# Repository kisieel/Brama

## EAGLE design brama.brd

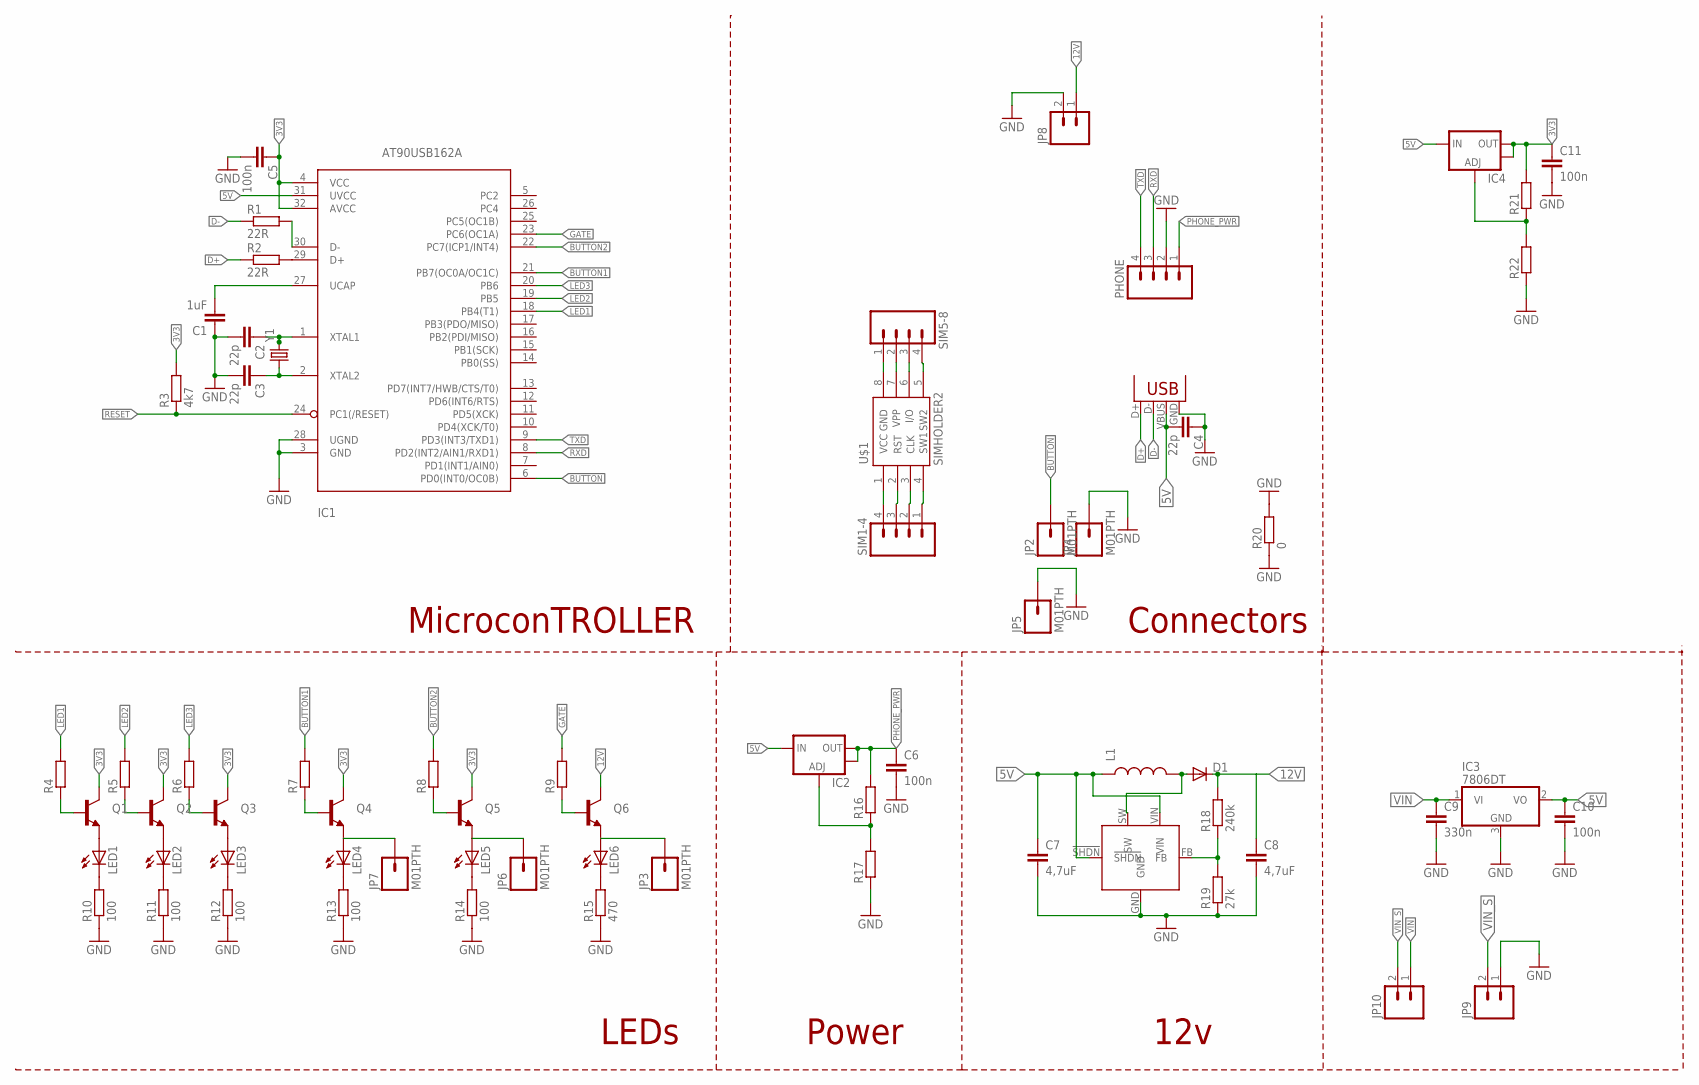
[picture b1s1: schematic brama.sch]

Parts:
C1: 1uF; C0805
C2, C3, C4: 22p; C0805
C5, C6, C10, C11: 100n; C0805
C7, C8: 4,7uF; C0805
C9: 330n; C0805
D1: DIODESMB; SMB-DIODE
IC1: AT90USB162A; TQFP32-08
IC2, IC4: V_REG_LM1117SOT223; SOT223
IC3: 7806DT; TO252
JP1: USBSMD; USB-MINIB
JP2, JP3, JP4, JP5, JP6, JP7: M01PTH; 1X01
JP8, JP9, JP10: M02PTH3; 1X02_LONGPADS
L1: INDUCTOR0805; 0805
LED1, LED2, LED3, LED4, LED5, LED6: LEDCHIPLED_0805; CHIPLED_0805
PHONE: M04LONGPADS; 1X04_LONGPADS
Q1, Q2, Q3, Q4, Q5, Q6: TRANSISTOR_NPNSOT23; SOT23
R1, R2: 22R; R0805
R3: 4k7; R0805
R4, R5, R6, R7, R8, R9, R16, R17, R21, R22: R-EU_R0805; R0805
R10, R11, R12, R13, R14: 100; R0805
R15: 470; R0805
R18: 240k; R0805
R19: 27k; R0805
R20: 0; R0805
SIM1-4, SIM5-8: M04LONGPADS; 1X04_LONGPADS
U$1: SIMHOLDER2
U$6: LM2704MF-ADJ; SOT23-5
Y1: CRYSTALSMD; HC49UP

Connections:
3V3: C5.1, C11.1, IC1.4 (VCC), IC1.32 (AVCC), IC4.2 (OUT), IC4.4 (OUT), Q1.3 (C), Q2.3 (C), Q3.3 (C), Q4.3 (C), Q5.3 (C), R3.2, R21.2
5V: C4.2, C7.1, C10.1, IC1.31 (UVCC), IC2.3 (IN), IC3.2 (VO), IC4.3 (IN), JP1.VBUS, L1.1, U$6.!SHDN, U$6.VIN
12V: C8.1, D1.C, JP8.1, Q6.3 (C), R18.2
BUTTON: IC1.6 (PD0(INT0/OC0B)), JP2.1
BUTTON1: IC1.21 (PB7(OC0A/OC1C)), R7.2
BUTTON2: IC1.22 (PC7(ICP1/INT4)), R8.2
D+: JP1.D+, R2.1
D-: JP1.D-, R1.1
GATE: IC1.23 (PC6(OC1A)), R9.2
GND: C1.1, C2.2, C3.2, C4.1, C5.2, C6.2, C7.2, C8.2, C9.2, C10.2, C11.2, IC1.3 (GND), IC1.28 (UGND), IC3.3 (GND), JP1.GND, JP4.1, JP5.1, JP8.2, JP9.1, PHONE.2, R10.1, R11.1, R12.1, R13.1, R14.1, R15.1, R17.1, R19.1, R20.1, R20.2, R22.1, U$6.GND
LED1: IC1.18 (PB4(T1)), R4.2
LED2: IC1.19 (PB5), R5.2
LED3: IC1.20 (PB6), R6.2
unnamed: IC1.30 (D-), R1.2
unnamed: IC1.29 (D+), R2.2
unnamed: C2.1, IC1.1 (XTAL1), Y1.2
unnamed: C3.1, IC1.2 (XTAL2), Y1.1
unnamed: SIM1-4.4, U$1.1 (VCC)
unnamed: LED1.A, Q1.2 (E)
unnamed: LED2.A, Q2.2 (E)
unnamed: LED3.A, Q3.2 (E)
unnamed: JP7.1, LED4.A, Q4.2 (E)
unnamed: JP6.1, LED5.A, Q5.2 (E)
unnamed: JP3.1, LED6.A, Q6.2 (E)
unnamed: Q1.1 (B), R4.1
unnamed: Q2.1 (B), R5.1
unnamed: Q3.1 (B), R6.1
unnamed: Q4.1 (B), R7.1
unnamed: Q5.1 (B), R8.1
unnamed: Q6.1 (B), R9.1
unnamed: LED1.C, R10.2
unnamed: LED2.C, R11.2
unnamed: LED3.C, R12.2
unnamed: LED4.C, R13.2
unnamed: LED5.C, R14.2
unnamed: LED6.C, R15.2
unnamed: SIM5-8.1, U$1.8 (GND)
unnamed: SIM5-8.2, U$1.7 (VPP)
unnamed: SIM5-8.3, U$1.6 (I/O)
unnamed: SIM5-8.4, U$1.5 (SW2)
unnamed: SIM1-4.1, U$1.4 (SW1)
unnamed: SIM1-4.2, U$1.3 (CLK)
unnamed: SIM1-4.3, U$1.2 (RST)
unnamed: D1.A, L1.2, U$6.SW
unnamed: IC2.1 (ADJ), R16.1, R17.2
unnamed: IC4.1 (ADJ), R21.1, R22.2
unnamed: R18.1, R19.2, U$6.FB
PHONE_PWR: C6.1, IC2.2 (OUT), IC2.4 (OUT), PHONE.1, R16.2
RESET: IC1.24 (PC1(/RESET)), R3.1
RXD: IC1.8 (PD2(INT2/AIN1/RXD1)), PHONE.3
TXD: IC1.9 (PD3(INT3/TXD1)), PHONE.4
UCAP: C1.2, IC1.27 (UCAP)
VIN: C9.1, IC3.1 (VI), JP10.1
VIN_S: JP9.2, JP10.2

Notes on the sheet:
MicroconTROLLER
Connectors
LEDs
Power
12v

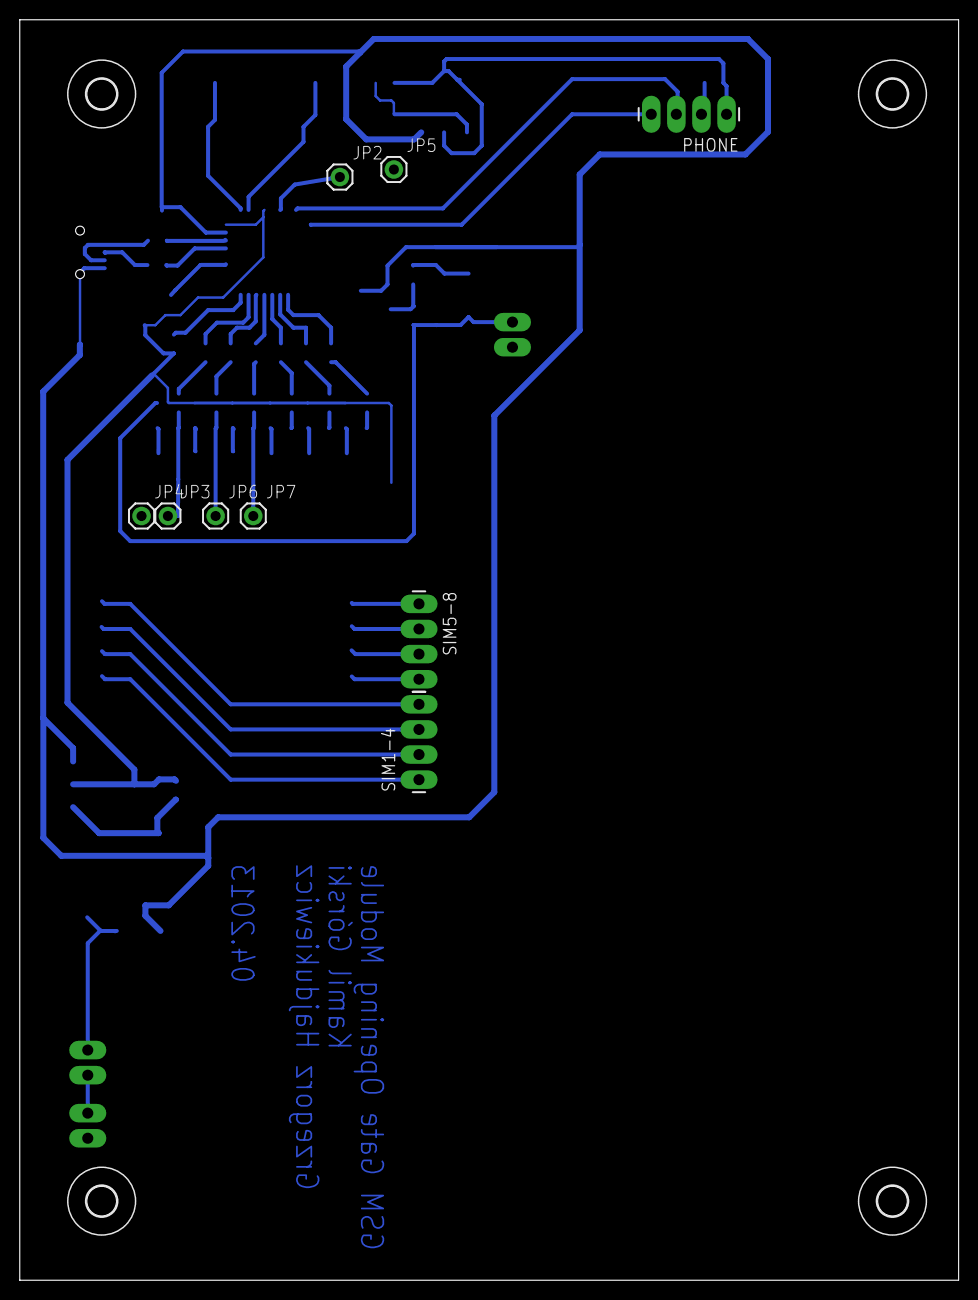
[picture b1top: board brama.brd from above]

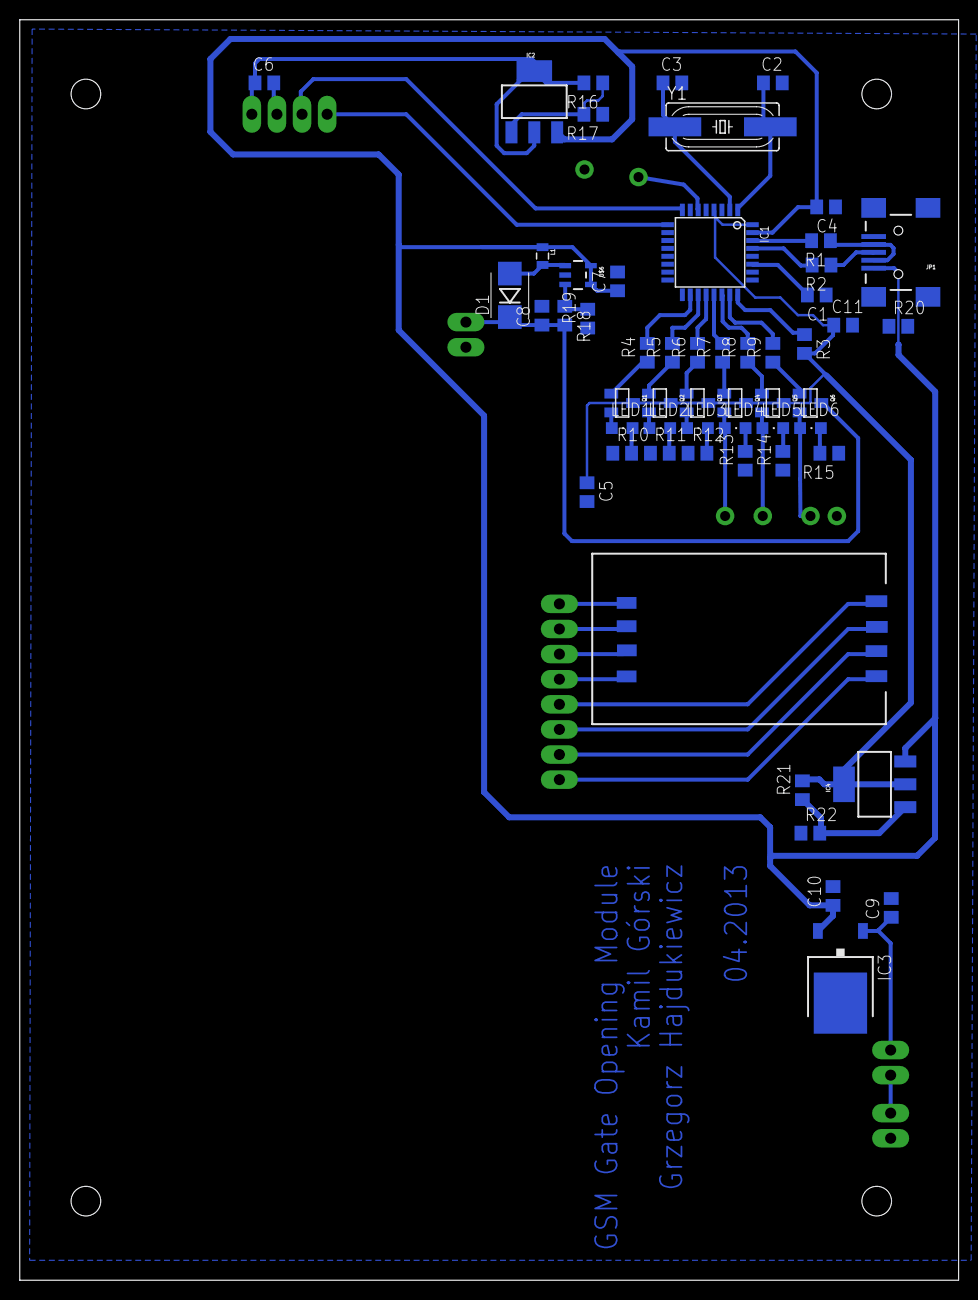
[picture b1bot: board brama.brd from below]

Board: 2 copper layers, 95.0 x 127.5 mm, 71 parts (55 on the bottom side), 54 nets.

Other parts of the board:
U$2, U$3, U$4, U$5: 3,0

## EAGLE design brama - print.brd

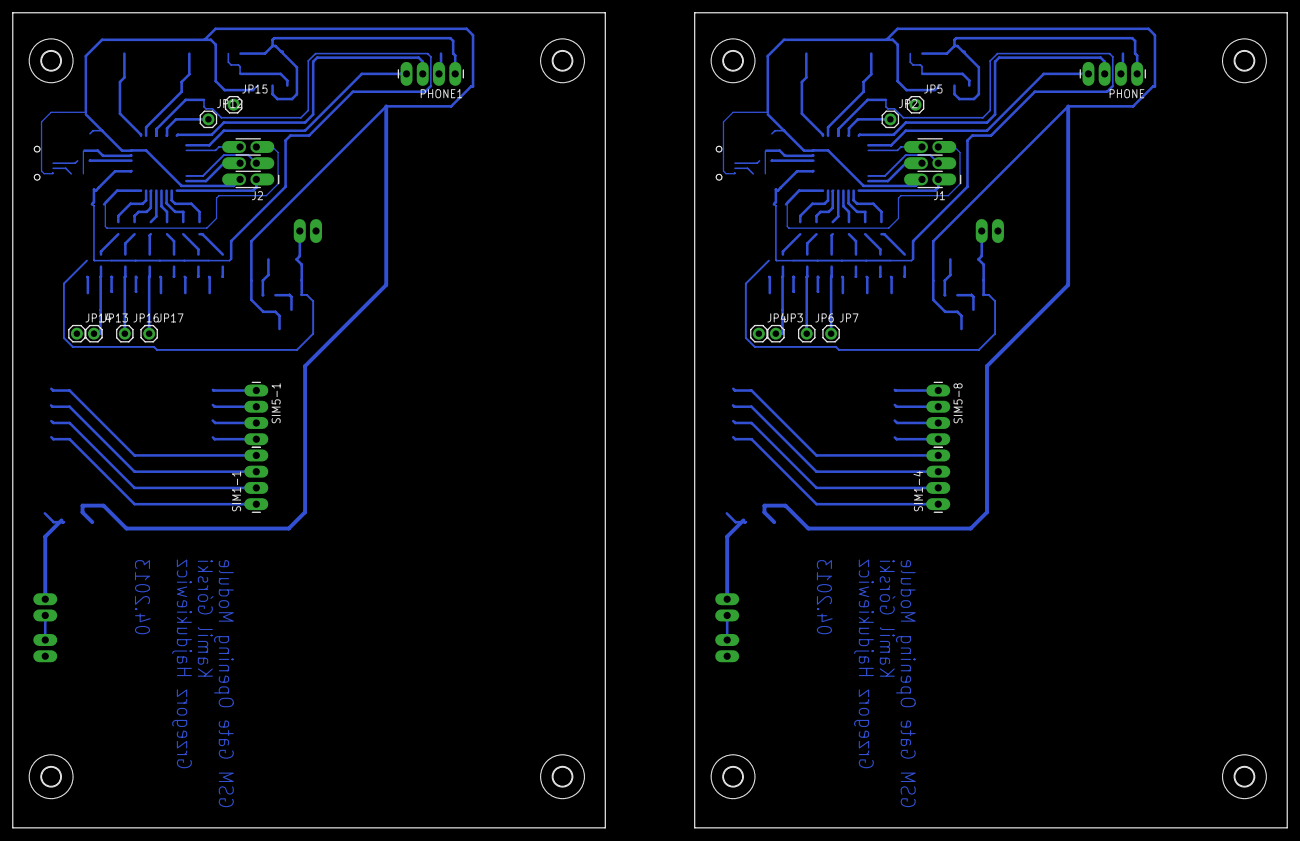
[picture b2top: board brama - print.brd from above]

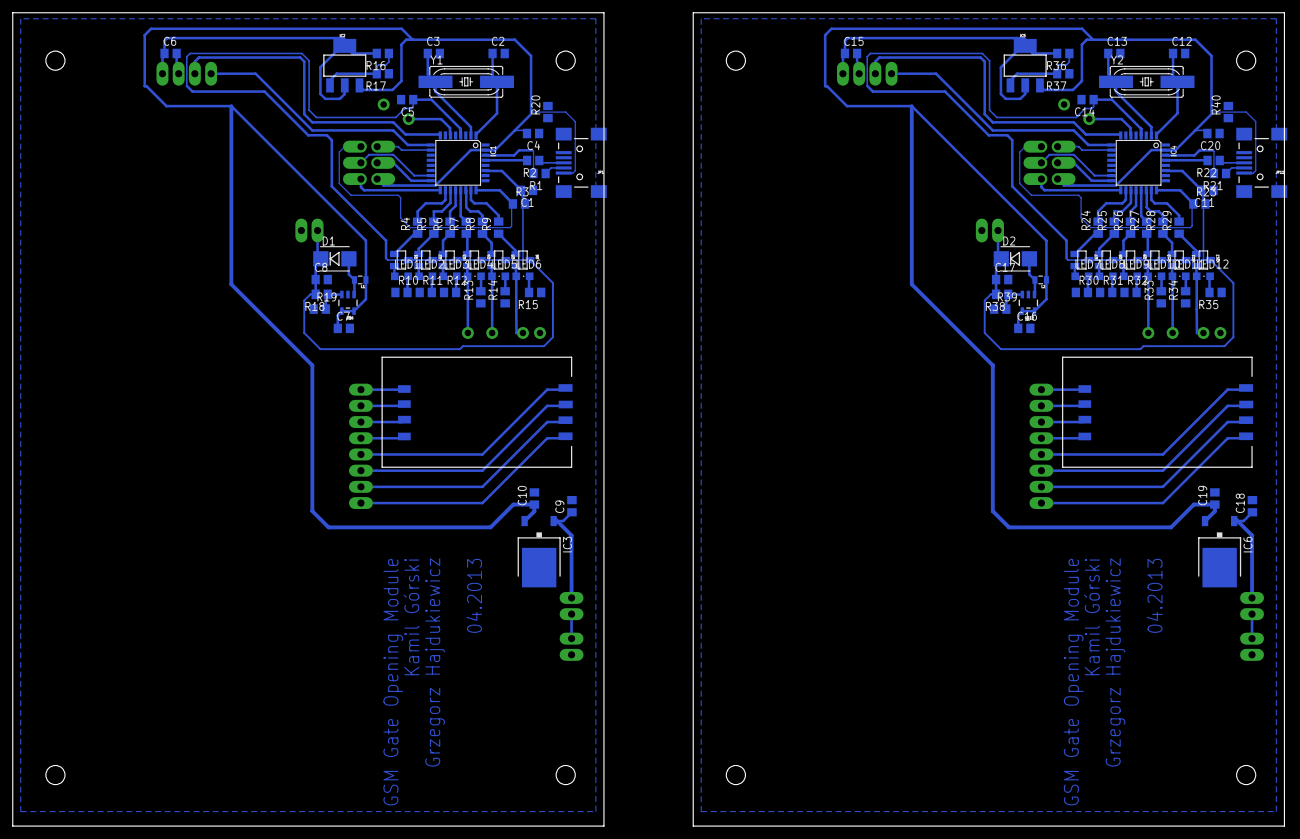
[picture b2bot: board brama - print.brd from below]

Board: 2 copper layers, 199.4 x 127.5 mm, 137 parts (102 on the bottom side), 110 nets.

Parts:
C1, C11: 1uF; C0805
C2, C3, C4, C12, C13, C20: 22p; C0805
C5, C6, C10, C14, C15, C19: 100n; C0805
C7, C8, C16, C17: 4,7uF; C0805
C9, C18: 330n; C0805
D1, D2: SMB-DIODE
E$1: A4P-LOC
IC1, IC4: AT90USB162A; TQFP32-08
IC2, IC5: SOT223
IC3, IC6: 7806DT; TO252
J1, J2: AVR_SPI_PRG_6OFFSET_PADS; 2X3_OFFSET
JP1, JP11: USBSMD; USB-MINIB
JP2, JP3, JP4, JP5, JP6, JP7, JP12, JP13, JP14, JP15, JP16, JP17: M01PTH; 1X01
JP8, JP9, JP10, JP18, JP19, JP20: 1X02_LONGPADS
L1, L2: 0805
LED1, LED2, LED3, LED4, LED5, LED6, LED7, LED8, LED9, LED10, LED11, LED12: CHIPLED_0805
PHONE, PHONE1: 1X04_LONGPADS
Q1, Q2, Q3, Q4, Q5, Q6, Q7, Q8, Q9, Q10, Q11, Q12: SOT23
R1, R2, R21, R22: 22R; R0805
R3, R23: 4k7; R0805
R4, R5, R6, R7, R8, R9, R16, R17, R24, R25, R26, R27, R28, R29, R36, R37: R0805
R10, R11, R12, R13, R14, R30, R31, R32, R33, R34: 100; R0805
R15, R35: 470; R0805
R18, R38: 240k; R0805
R19, R39: 27k; R0805
R20, R40: 0; R0805
SIM1-1, SIM1-4, SIM5-1, SIM5-8: 1X04_LONGPADS
U$1, U$7: SIMHOLDER2
U$2, U$3, U$4, U$5, U$8, U$9, U$10, U$11: 3,0
U$6, U$12: LM2704MF-ADJ; SOT23-5
Y1, Y2: HC49UP

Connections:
3V1: C11.2, C14.1, IC4.4, IC4.27, Q7.3, Q8.3, Q9.3, Q10.3, Q11.3, R23.2
3V3: C1.2, C5.1, IC1.4, IC1.27, Q1.3, Q2.3, Q3.3, Q4.3, Q5.3, R3.2
5V: C4.2, C7.1, C10.1, IC1.31, IC2.3, IC3.2, J1.2, JP1.VBUS, L1.1, U$6.!SHDN, U$6.VIN
5V1: C16.1, C19.1, C20.2, IC4.31, IC5.3, IC6.2, J2.2, JP11.VBUS, L2.1, U$12.!SHDN, U$12.VIN
12V: C8.1, D1.C, JP8.1, Q6.3, R18.2
12V1: C17.1, D2.C, JP18.1, Q12.3, R38.2
BUTTON: IC1.6, JP2.1
BUTTON1: IC1.21, R7.2
BUTTON2: IC1.22, R8.2
BUTTON3: IC4.6, JP12.1
BUTTON4: IC4.21, R27.2
BUTTON5: IC4.22, R28.2
D+: JP1.D+, R2.1
D+1: JP11.D+, R22.1
D-: JP1.D-, R1.1
D-1: JP11.D-, R21.1
GATE: IC1.23, R9.2
GATE1: IC4.23, R29.2
GND: C1.1, C2.2, C3.2, C4.1, C5.2, C6.2, C7.2, C8.2, C9.2, C10.2, IC1.3, IC1.10, IC1.28, IC3.3, J1.6, JP1.GND, JP4.1, JP5.1, JP8.2, JP9.1, PHONE.2, R10.1, R11.1, R12.1, R13.1, R14.1, R15.1, R17.1, R19.1, R20.1, R20.2, U$6.GND
GND1: C11.1, C12.2, C13.2, C14.2, C15.2, C16.2, C17.2, C18.2, C19.2, C20.1, IC4.3, IC4.10, IC4.28, IC6.3, J2.6, JP11.GND, JP14.1, JP15.1, JP18.2, JP19.1, PHONE1.2, R30.1, R31.1, R32.1, R33.1, R34.1, R35.1, R37.1, R39.1, R40.1, R40.2, U$12.GND
LED1: IC1.18, R4.2
LED2: IC1.19, R5.2
LED3: IC1.20, R6.2
LED4: IC4.18, R24.2
LED5: IC4.19, R25.2
LED6: IC4.20, R26.2
MISO: IC1.17, J1.1
MISO1: IC4.17, J2.1
MOSI: IC1.16, J1.4
MOSI1: IC4.16, J2.4
unnamed: IC1.30, R1.2
unnamed: IC1.29, R2.2
unnamed: C2.1, IC1.1, Y1.2
unnamed: C3.1, IC1.2, Y1.1
unnamed: SIM1-4.4, U$1.1
unnamed: LED1.A, Q1.2
unnamed: LED2.A, Q2.2
unnamed: LED3.A, Q3.2
unnamed: JP7.1, LED4.A, Q4.2
unnamed: JP6.1, LED5.A, Q5.2
unnamed: JP3.1, LED6.A, Q6.2
unnamed: Q1.1, R4.1
unnamed: Q2.1, R5.1
unnamed: Q3.1, R6.1
unnamed: Q4.1, R7.1
unnamed: Q5.1, R8.1
unnamed: Q6.1, R9.1
unnamed: LED1.C, R10.2
unnamed: LED2.C, R11.2
unnamed: LED3.C, R12.2
unnamed: LED4.C, R13.2
unnamed: LED5.C, R14.2
unnamed: LED6.C, R15.2
unnamed: SIM5-8.1, U$1.8
unnamed: SIM5-8.2, U$1.7
unnamed: SIM5-8.3, U$1.6
unnamed: SIM5-8.4, U$1.5
unnamed: SIM1-4.1, U$1.4
unnamed: SIM1-4.2, U$1.3
unnamed: SIM1-4.3, U$1.2
unnamed: D1.A, L1.2, U$6.SW
unnamed: IC2.1, R16.1, R17.2
unnamed: IC4.30, R21.2
unnamed: R18.1, R19.2, U$6.FB
unnamed: IC4.29, R22.2
unnamed: C13.1, IC4.2, Y2.1
unnamed: LED7.A, Q7.2
unnamed: LED8.A, Q8.2
unnamed: LED9.A, Q9.2
unnamed: JP17.1, LED10.A, Q10.2
unnamed: JP16.1, LED11.A, Q11.2
unnamed: JP13.1, LED12.A, Q12.2
unnamed: Q7.1, R24.1
unnamed: Q8.1, R25.1
unnamed: Q9.1, R26.1
unnamed: Q10.1, R27.1
unnamed: Q11.1, R28.1
unnamed: Q12.1, R29.1
unnamed: LED7.C, R30.2
unnamed: LED8.C, R31.2
unnamed: LED9.C, R32.2
unnamed: LED10.C, R33.2
unnamed: LED11.C, R34.2
unnamed: LED12.C, R35.2
unnamed: C12.1, IC4.1, Y2.2
unnamed: SIM1-1.4, U$7.1
unnamed: SIM5-1.1, U$7.8
unnamed: SIM5-1.2, U$7.7
unnamed: SIM5-1.3, U$7.6
unnamed: SIM5-1.4, U$7.5
unnamed: SIM1-1.1, U$7.4
unnamed: SIM1-1.2, U$7.3
unnamed: SIM1-1.3, U$7.2
unnamed: IC5.1, R36.1, R37.2
unnamed: R38.1, R39.2, U$12.FB
unnamed: D2.A, L2.2, U$12.SW
PHONE_PWR: C6.1, IC2.2, IC2.4, PHONE.1, R16.2
PHONE_PWR1: C15.1, IC5.2, IC5.4, PHONE1.1, R36.2
RESET: IC1.24, J1.5, R3.1
RESET1: IC4.24, J2.5, R23.1
RXD: IC1.8, PHONE.3
RXD1: IC4.8, PHONE1.3
SCK: IC1.15, J1.3
SCK1: IC4.15, J2.3
TXD: IC1.9, PHONE.4
TXD1: IC4.9, PHONE1.4
VIN: C9.1, IC3.1, JP10.1
VIN1: C18.1, IC6.1, JP20.1
VIN_S: JP9.2, JP10.2
VIN_S1: JP19.2, JP20.2

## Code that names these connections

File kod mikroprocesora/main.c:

#include "main.h"


USB_ClassInfo_CDC_Device_t VirtualSerial_CDC_Interface =
	{
		.Config =
			{
				.ControlInterfaceNumber   = 0,
				.DataINEndpoint           =
					{
						.Address          = CDC_TX_EPADDR,
						.Size             = CDC_TXRX_EPSIZE,
						.Banks            = 1,
					},
				.DataOUTEndpoint =
					{
						.Address          = CDC_RX_EPADDR,
						.Size             = CDC_TXRX_EPSIZE,
						.Banks            = 1,
					},
				.NotificationEndpoint =
					{
						.Address          = CDC_NOTIFICATION_EPADDR,
						.Size             = CDC_NOTIFICATION_EPSIZE,
						.Banks            = 1,
					},
			},
	};

static FILE USBSerialStream;
static volatile int16_t phoneBuffer[100];
static volatile int16_t bufferLength = 1;
static volatile int16_t callingNumber[10];
static volatile int16_t numbers = 0;
volatile static bool bDebug = false;
volatile int16_t iRead = 0;
volatile static bool ConfigSuccess = true;

void uart_put( unsigned char data )
{
	 while(!(UCSR1A & (1<<UDRE1)));
		UDR1=data;		        
}

void uart_puts(const char *s )
{
    while (*s)
      uart_put(*s++);
}

unsigned char uart_get( void ) 
{
	while ( !(UCSR1A & (1<<RXC1)) );
	return UDR1;
}

unsigned char stringCheck(char *s)
{
	int i = 1;
	while (*s)
	{		
		if(phoneBuffer[i] != *s++)
			return 0;
		i++;			
	}
	
	return 1;
}

void openGate()
{
	PORTC |= (1 << PC6);
	_delay_ms(2000);
	PORTC &= ~(1 << PC6);
}
unsigned char checkNumber(int corr)
{
	for(int i = 0; i < 9; i++)
	{
		if(callingNumber[i] != phoneBuffer[i + 23 + (2*corr)])
			return 0;
	}	
	
	return 1;
}

void bufferCheck()
{
	if(bufferLength > 7 && stringCheck("\r\nRING\r\n") == 1)
	{		
		if(PIND & (1 << PD0)) // tryb wpuszczaj wybranych
		{		
			uart_puts("AT+CLCC\r");
			_delay_ms(200);
			
			for(int i = 40; i < 49; i++)
				callingNumber[i - 40] = phoneBuffer[i];
				
			for(int num = 1; num < numbers + 1; num++)
			{
				char buff[5];
				itoa(num, buff, 10);
				
				int korekcja = 0;				
				if(num > 99)
				{
					korekcja = 2;
				}
				else if(num > 9)
				{
					korekcja = 1;
				}
				
						
				bufferLength = 1;	
				uart_puts("AT+CPBR=");
				
				for(int i = 0; i < korekcja+1; i++)
					uart_put(buff[i]);
				
				uart_put('\r');
				
				_delay_ms(300);
		
				
				if(checkNumber(korekcja) == 1)
				{
					openGate();
					break;
				}
				
			}
		
		}		
		else // wpuszaczaj wszystkich
		{
			openGate();
		}			
		
		bufferLength = 1;			
		
		uart_puts("AT+CHUP\r");
		_delay_ms(500);
		bufferLength = 1;	
	}

}

SIGNAL(USART1_RX_vect)
{
	int16_t c = UDR1;
	if(bDebug && ConfigSuccess)
		fputs(&c, &USBSerialStream); // do debugu
	
	phoneBuffer[bufferLength] = c;
	bufferLength++;		
}

void TelephoneInit()
{	
	uart_puts("AT+CGMI\r");
	
	_delay_ms(1000);
	
	if(bufferLength < 5)
	{	

		PORTB |= (1 << PB7);
		_delay_ms(1000);
		PORTB &= ~(1 << PB7);
		_delay_ms(1000);
		PORTB |= (1 << PB7);
		_delay_ms(1000);
		PORTB &= ~(1 << PB7);
		_delay_ms(4000);
		PORTC |= (1 << PC7);
		_delay_ms(200);
		PORTC &= ~(1 << PC7);
		_delay_ms(1000);
		PORTC |= (1 << PC7);
		_delay_ms(200);
		PORTC &= ~(1 << PC7);
		
		_delay_ms(1000);
		uart_puts("AT+CGMI\r");
		_delay_ms(1000);
	}

	bufferLength = 1;

}
int main(void)
{
	SetupHardware();	 
	
	CDC_Device_CreateStream(&VirtualSerial_CDC_Interface, &USBSerialStream);
	
	GlobalInterruptEnable();
	
	_delay_ms(1000);
	
	TelephoneInit(); 
	
	numbers = eeprom_read_word(( uint16_t *)1) ;

	for (;;)
	{
	
		if(ConfigSuccess)
		{
			int16_t b = CDC_Device_ReceiveByte(&VirtualSerial_CDC_Interface);
			
			if(b > -1)
			{
					
				if(b == '*')
					iRead = 0;	
				
				if(b == 0x1A)
				{
					numbers = iRead;
					eeprom_write_word((uint16_t*)1, (uint16_t)numbers);
				}			
					
				if(b == '\r' || b == 0x1A)
				{
					uart_put('\r');
					_delay_ms(300);
					bufferLength = 1;
					
					fputs("ok\r\n", &USBSerialStream);
				}
				
				if(b == '*' || b == '\r')
				{
					iRead++;
					uart_puts("AT+CPBW=");
					
					char buff[5];
					itoa(iRead, buff, 10);
					
					int korekcja = 0;				
					if(iRead > 99)
					{
						korekcja = 2;
					}
					else if(iRead > 9)
					{
						korekcja = 1;
					}
					
					for(int i = 0; i < korekcja+1; i++)
						uart_put(buff[i]);
						
					uart_put(',');
				}

				if(b > 47 && b < 58)
				{
					uart_put(b);			
				}
				
				if(b == 0x1B)
					openGate();
					
				if(b == 'd')
					bDebug = !bDebug;
									
			}
			
			CDC_Device_USBTask(&VirtualSerial_CDC_Interface);
			USB_USBTask();
		}
			
		bufferCheck();
			
	}
}

void USARTInit(unsigned int ubrr_value)
{   
   UCSR1A |= (1 << U2X1);
   UCSR1B |= (1 << RXEN1) | (1 << TXEN1) | (1 << RXCIE1);
   UCSR1C |= (1 << UCSZ11) | (1 << UCSZ10);
   UBRR1 = ubrr_value;
   DDRD |= (1 << PD3);
}

void SetupHardware(void)
{
	MCUSR &= ~(1 << WDRF);
	wdt_disable();	
	
	DDRB = (1 << PB5) | (1 << PB7) | (1 << PB4) | (1 << PB6);	
	DDRC = (1 << PC6) | (1 << PC7);	//ledy i buttony
	
	DDRD &= ~(1 << PD0);
	PORTD |= (1 << PD0); // wybor trybu

	clock_prescale_set(clock_div_1);

	USB_Init();
	
	USARTInit(103);
}

void EVENT_USB_Device_Connect(void)
{
	PORTB |= (1 << PB4);
	PORTB &= ~((1 << PB5) | (1 << PB6));
}

void EVENT_USB_Device_Disconnect(void)
{
	PORTB |= (1 << PB5);
	PORTB &= ~((1 << PB4) | (1 << PB6));
}

void EVENT_USB_Device_ConfigurationChanged(void)
{
	ConfigSuccess &= CDC_Device_ConfigureEndpoints(&VirtualSerial_CDC_Interface);
	
	if(ConfigSuccess)
	{
		PORTB |= (1 << PB5) | (1 << PB4) | (1 << PB6);
	}
	else
	{
		PORTB |= (1 << PB6);
		PORTB &= ~((1 << PB5) | (1 << PB4));
	}
}

void EVENT_USB_Device_ControlRequest(void)
{
	CDC_Device_ProcessControlRequest(&VirtualSerial_CDC_Interface);
}

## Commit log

2013-04-07 Schematic + PCB Layout
2013-04-07 Git Ignore Update
2013-04-08 większe miejsce na fona
2013-04-08 Mounting Holes + Autor Sign + AT Command Set PDF
2013-04-14 DC-DC converter
2013-04-14 Gitignore Changes
2013-04-15 LM2704 Step-Up DC/DC Converter
    http://www.ti.com.cn/general/cn/docs/lit/getliterature.tsp?genericPartNumber=lm2704&fileType=pdf
2013-04-20 L7805 Added
2013-04-22 USB socket Change
2013-04-25 nowy druk
2013-04-27 poprawki
2013-05-12 piszemy soft
2013-05-12 pierwsza wersja GUI
2013-05-13 apka na szybko
2013-05-13 brakujące pliki
2013-05-13 Driver Update
2013-05-22 wpuszczanie działa
    porównywanie numerów z książką telefonu i tryb wpuszczaj wszystkich
2013-05-22 poprawka dla wpisów w książce > 10
2013-05-23 wgrywanie numerów
    i lekki pimp apki
2013-05-23 poprawka buga od przycisku
2013-05-25 poprawki apki desktopowej

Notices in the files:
parts and their libraries:
SparkFun-Connectors: Licensing: CC v3.0 Share-Alike You are welcome to use this library for commercial purposes.
